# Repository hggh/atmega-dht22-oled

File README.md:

# atmega-dht22-oled

Platine mit Atmega328, angeschlossen an ein oLED Display und einem DHT22.

Stromversorgung über eine USB Buchse.

## Bauteile

  * 1x Atmega328
  * 1x 0,96" oLED Display
  * 1x DHT22
  * 2x 22pF Transistor
  * 1x 16MHz Quarz
  * 2x Widerstand 10k Ohm
  * 1x Widerstand 220 Ohm
  * 1x USB B Buchse (Lötmontage)

## Gehäuse

Geplant ist ein Gehäuse mit 2mm Plastikplatten.

## Gerber Plot von Kicad zu OSH Park

```
front=$(ls  *-F.Cu.gbr)
projname=$(basename $front \-F.Cu.gbr)

mv *-F.Cu.gbr $projname.GTL
mv *-B.Cu.gbr $projname.GBL
mv *-F.Mask.gbr $projname.GTS
mv *-B.Mask.gbr $projname.GBS
mv *-F.SilkS.gbr $projname.GTO
mv *-B.SilkS.gbr $projname.GBO
mv *-Edge.Cuts.gbr $projname.GKO
mv *.drl $projname.XLN
```

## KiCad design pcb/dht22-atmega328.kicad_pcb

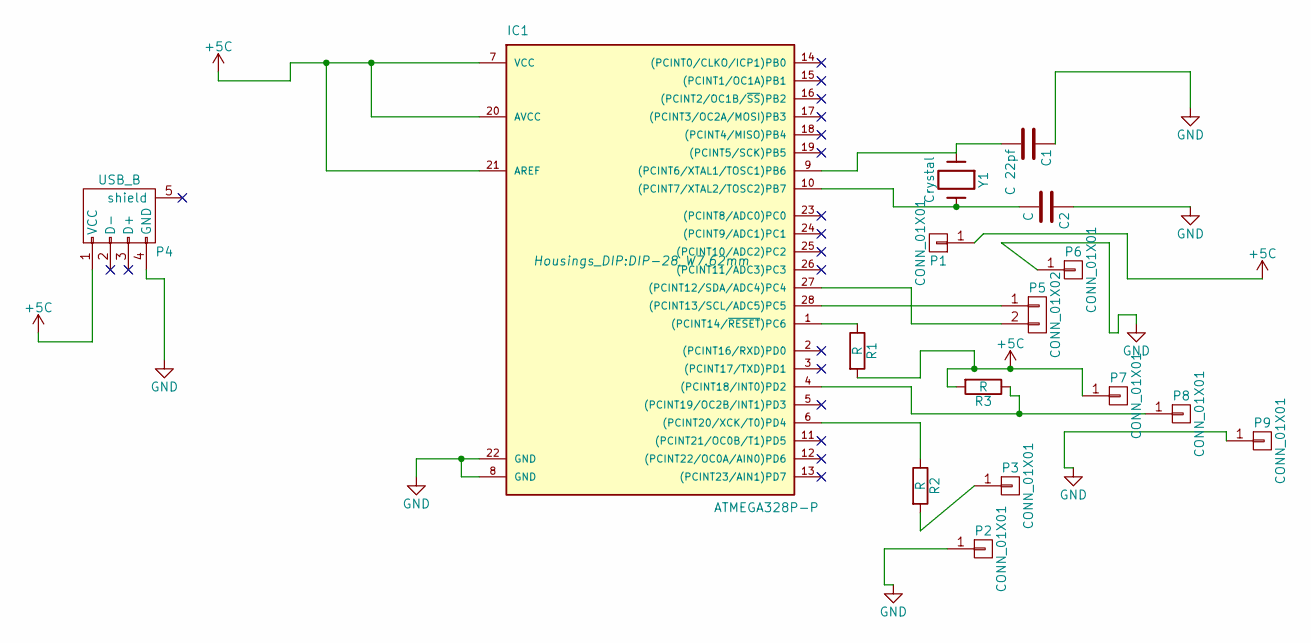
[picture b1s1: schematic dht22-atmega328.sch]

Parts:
C1: C 22pf; C_Rect_L7_W2_P5
C2: C; C_Rect_L7_W2_P5
IC1: ATMEGA328P-P; DIP-28_W7.62mm
P1, P2, P3, P6, P7, P8, P9: CONN_01X01; Pin_Header_Straight_1x01
P4: USB_B
P5: CONN_01X02; Pin_Header_Straight_1x02
R1, R2, R3: R; Resistor_Horizontal_RM10mm
Y1: Crystal; Crystal_HC50-U_Vertical

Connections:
+5C: IC1.7 (VCC), IC1.20 (AVCC), IC1.21 (AREF), P1.1, P4.1 (VCC), P7.1, R1.2, R3.2
GND: C1.1, C2.1, IC1.8 (GND), IC1.22 (GND), P2.1, P4.4 (GND), P6.1, P9.1
unnamed: C1.2, IC1.9 ((PCINT6/XTAL1/TOSC1)PB6), Y1.1
unnamed: C2.2, IC1.10 ((PCINT7/XTAL2/TOSC2)PB7), Y1.2
unnamed: IC1.1 ((PCINT14/~RESET~)PC6), R1.1
unnamed: IC1.4 ((PCINT18/INT0)PD2), P8.1, R3.1
unnamed: IC1.6 ((PCINT20/XCK/T0)PD4), R2.1
unnamed: IC1.27 ((PCINT12/SDA/ADC4)PC4), P5.2
unnamed: IC1.28 ((PCINT13/SCL/ADC5)PC5), P5.1
unnamed: P3.1, R2.2

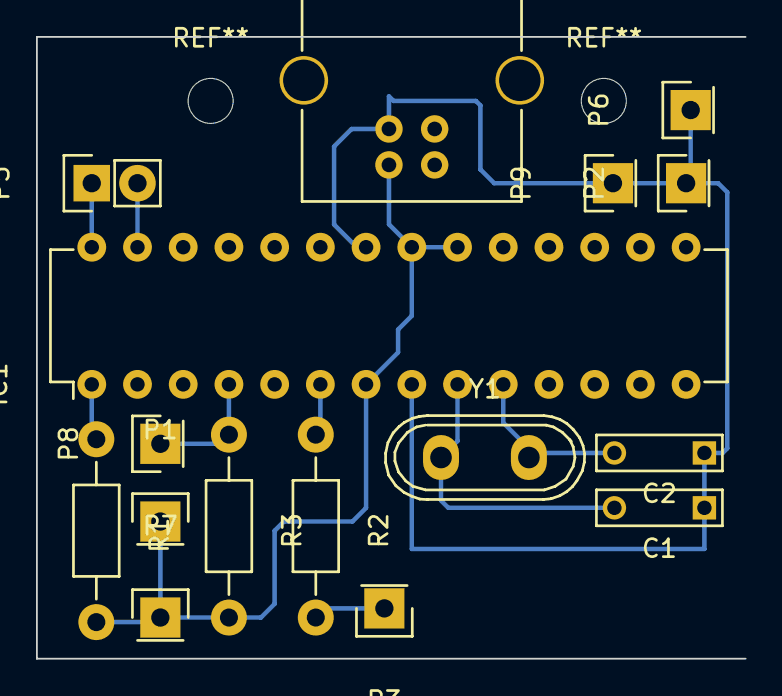
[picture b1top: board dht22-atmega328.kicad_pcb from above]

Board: 2 copper layers, 39.4 x 34.5 mm, 16 parts (0 on the bottom side), 10 nets.

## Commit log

2016-04-01 added lcb
2016-04-01 added src
2016-04-01 added readme
2016-04-01 fix pcb
2016-04-01 added info for OSH park upload
2016-04-21 added papercut
2018-03-17 added with is471 sensor
